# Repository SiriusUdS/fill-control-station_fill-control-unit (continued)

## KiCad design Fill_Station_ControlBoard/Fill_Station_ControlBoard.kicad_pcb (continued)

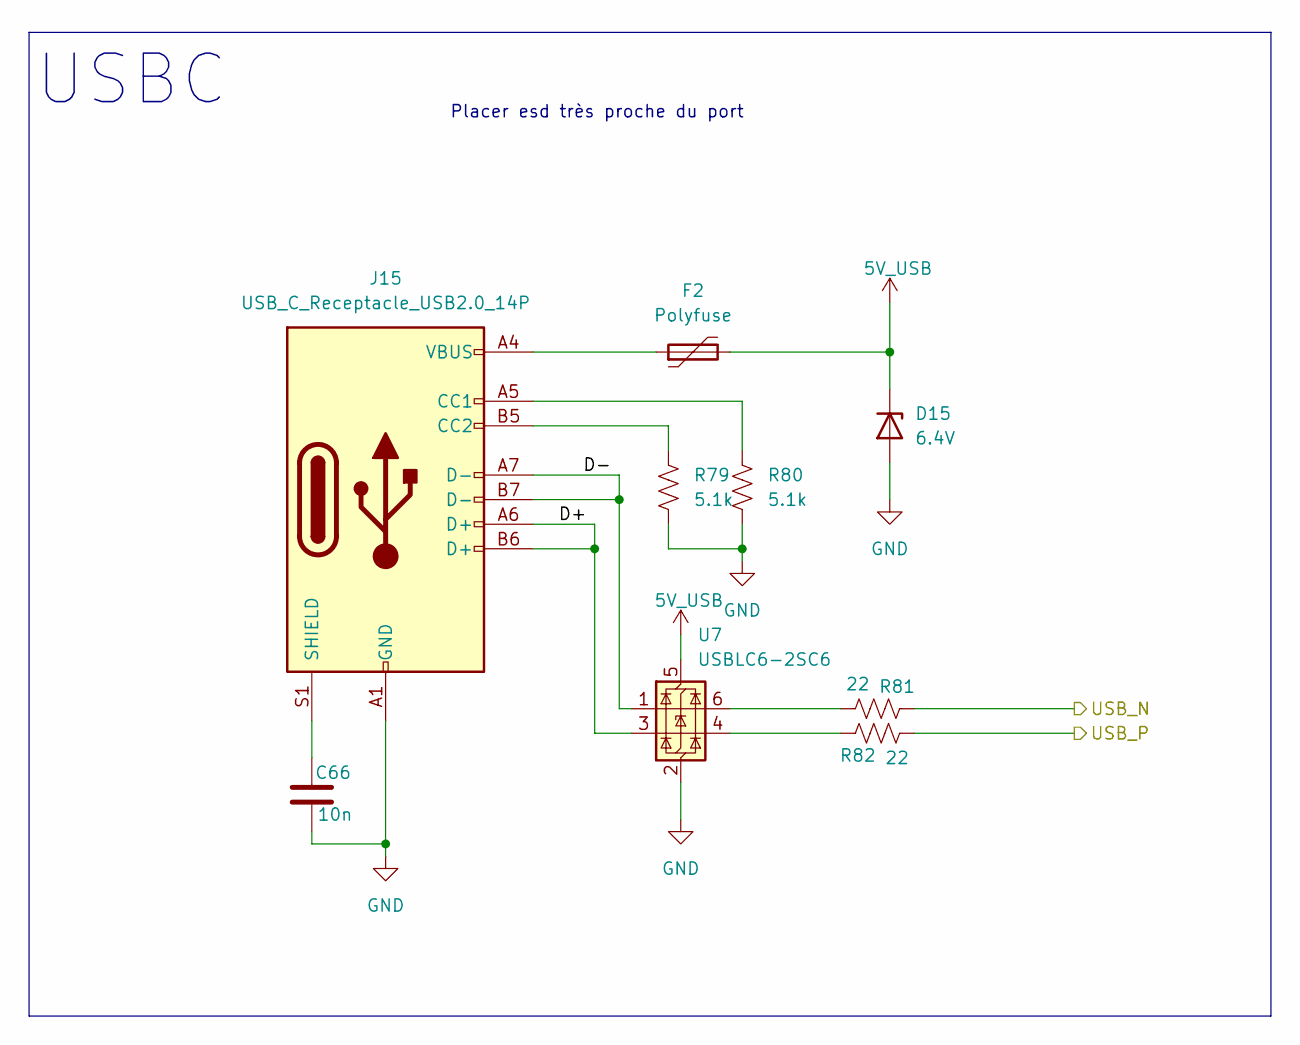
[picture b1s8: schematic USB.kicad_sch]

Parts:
C66: 10n; C_0603_1608Metric; LCSC C100042
D15: 6.4V; D_SOD-123; LCSC C79598
F2: Polyfuse; Fuse_1206_3216Metric; LCSC C70083
J15: USB_C_Receptacle_USB2.0_14P; USB_C_Receptacle_GCT_USB4105-xx-A_16P_TopMnt_Horizontal; LCSC C393939
R79, R80: 5.1k; R_0402_1005Metric; LCSC C25905
R81, R82: 22; R_0402_1005Metric; LCSC C25092
U7: USBLC6-2SC6; SOT-23-6; LCSC C7519

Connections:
5V_USB: D15.1 (K), F2.2, U7.5 (VBUS); also elsewhere on the board
/MCU/USBC.DM: R81.1; also elsewhere on the board
/MCU/USBC.DP: R82.2; also elsewhere on the board
/USB/D+: J15.A6 (D+), J15.B6 (D+), U7.3 (I/O2)
/USB/D-: J15.A7 (D-), J15.B7 (D-), U7.1 (I/O1)
GND: C66.2, D15.2 (A), J15.A1 (GND), J15.A12 (GND), J15.B1 (GND), J15.B12 (GND), R79.2, R80.2, U7.2 (GND); also elsewhere on the board
unnamed: F2.1, J15.A4 (VBUS), J15.A9 (VBUS), J15.B4 (VBUS), J15.B9 (VBUS)
unnamed: J15.A5 (CC1), R80.1
unnamed: J15.B5 (CC2), R79.1
unnamed: C66.1, J15.S1 (SHIELD)
unnamed: R81.2, U7.6 (I/O1)
unnamed: R82.1, U7.4 (I/O2)

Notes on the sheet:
Placer esd très proche du port
USBC

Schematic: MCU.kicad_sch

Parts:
BT1: RTC_BAT; Battery_Panasonic_CR2032-HFN_Horizontal_CircularHoles; Manufacturer Part Number BHX1-1025-SM; LCSC C910763
C16, C23, C25, C26, C27, C28, C29, C30, C31, C33, C34, C35, C36, C37, C39, C40, C41, C42, C43, C44, C46, C48, C83, C90, C91: 100n; C_0402_1005Metric; LCSC C60474
C17, C18, C19, C21: 2.2u; C_0603_1608Metric
C20: 100n; C_0603_1608Metric; LCSC C14663
C22, C45, C47, C50, C53: 1u; C_0603_1608Metric; LCSC C59302
C24, C54: 4.7u; C_0603_1608Metric; LCSC C108342
C49, C52, C87: 10u; C_0603_1608Metric; LCSC C22399626
C51: *; C_0402_1005Metric; not fitted
C88: 100u; C_0805_2012Metric; LCSC C141660
FID1, FID2, FID3: Fiducial; Fiducial_0.5mm_Mask1mm
H1, H2, H3, H4: M3_Hole_With_Spacer_H10mm; MountingHole_3.2mm_With_Spacer_H10mm
J12: Conn_02x05_Counter_Clockwise; PinSocket_2x05_P2.00mm_Vertical
L2: L_Ferrite; R_0402_1005Metric; LCSC C160977
R49, R50: 10k; R_0603_1608Metric
R51, R53: 10k; R_0402_1005Metric; LCSC C173683
R52: 10k; C_0402_1005Metric; LCSC C173683
R54: 0; R_0402_1005Metric; LCSC C17168
R89, R103, R113, R114: 22; R_0402_1005Metric; LCSC C25092
SW1: RESET; SW_DPDT_CK_JS202011JCQN; LCSC C221666
SW2: BOOT; SW_DPDT_CK_JS202011JCQN; LCSC C221666
U2: STM32H747IITx; LQFP-176_24x24mm_P0.5mm; LCSC C730199
Y1: ASV-25.000MHz; Oscillator_SMD_Abracon_ASV-4Pin_7.0x5.1mm; LCSC C1987509
Y2: ASV-32.768kHz; Oscillator_SMD_Abracon_ASV-4Pin_7.0x5.1mm; LCSC C17591433

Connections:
3V3: C24.1, C25.1, C26.1, C27.1, C28.1, C29.1, C30.1, C31.1, C33.1, C34.1, C35.1, C36.1, C37.1, C39.1, C40.1, C41.1, C42.1, C43.1, C44.1, C45.1, C46.1, C47.1, C48.1, C49.1, C50.1, C52.1, C53.1, C54.1, C87.1, C88.1, J12.1, L2.2, R51.1, R52.1, R53.1, SW1.3 (C), SW2.3 (C), U2.7 (VDD), U2.13 (VDD), U2.16 (VDDSMPS), U2.25 (VDD), U2.44 (VDD), U2.48 (VDD), U2.65 (VDD), U2.71 (VDD), U2.82 (VDDLDO), U2.84 (VDD), U2.92 (VDD), U2.99 (VDD), U2.113 (VDD), U2.121 (VDD33_USB), U2.126 (VDD), U2.135 (VDDLDO), U2.136 (VDD), U2.152 (VDD), U2.160 (VDD), U2.175 (VDDLDO), U2.176 (VDD), Y1.4 (Vdd), Y2.4 (Vdd); also elsewhere on the board
3V3A: C16.1, C83.1, L2.1, U2.39 (VREF+), U2.40 (VDDA)
5V: C22.1, C23.1, U2.120 (VDD50_USB); also elsewhere on the board
/Alimentation/LED1: U2.19 (PF1); also elsewhere on the board
/Alimentation/LED2: U2.20 (PF2); also elsewhere on the board
/Alimentation/LED3: U2.21 (PF3); also elsewhere on the board
/Alimentation/PM_CRIT: U2.59 (PF12); also elsewhere on the board
/Alimentation/PM_SCL: U2.61 (PF14); also elsewhere on the board
/Alimentation/PM_SDA: U2.62 (PF15); also elsewhere on the board
/Alimentation/PM_TC: U2.63 (PG0); also elsewhere on the board
/Alimentation/PM_WARN: U2.60 (PF13); also elsewhere on the board
/CAN FD/CAN.RXD: U2.168 (PB8); also elsewhere on the board
/CAN FD/CAN.TXD: R89.2; also elsewhere on the board
/Control/BUZZ: U2.91 (PD10); also elsewhere on the board
/Control/E-match1: U2.95 (PD12); also elsewhere on the board
/Control/E-match1_Cont: U2.89 (PD8); also elsewhere on the board
/Control/E-match1_Det: U2.96 (PD13); also elsewhere on the board
/Control/E-match2: U2.97 (PD14); also elsewhere on the board
/Control/E-match2_Cont: U2.90 (PD9); also elsewhere on the board
/Control/E-match2_Det: U2.98 (PD15); also elsewhere on the board
/Control/GPIO1: U2.1 (PE2); also elsewhere on the board
/Control/GPIO2: U2.2 (PE3); also elsewhere on the board
/Control/GPIO3: U2.3 (PE4); also elsewhere on the board
/Control/GPIO4: U2.4 (PE5); also elsewhere on the board
/Control/GPIO5: U2.5 (PE6); also elsewhere on the board
/Control/Servo.Signal1: U2.69 (PE9); also elsewhere on the board
/Control/Servo.Signal2: U2.68 (PE8); also elsewhere on the board
/Control/Servo.Signal3: U2.67 (PE7); also elsewhere on the board
/Ethernet/Eth.CRS_DV: U2.52 (PA7); also elsewhere on the board
/Ethernet/Eth.MDC: U2.35 (PC1); also elsewhere on the board
/Ethernet/Eth.MDIO: U2.43 (PA2); also elsewhere on the board
/Ethernet/Eth.REFCLKO: U2.42 (PA1); also elsewhere on the board
/Ethernet/Eth.RST: U2.51 (PA6); also elsewhere on the board
/Ethernet/Eth.RXD_N: U2.54 (PC5); also elsewhere on the board
/Ethernet/Eth.RXD_P: U2.53 (PC4); also elsewhere on the board
/Ethernet/Eth.TXD_N: R114.2; also elsewhere on the board
/Ethernet/Eth.TXD_P: R113.2; also elsewhere on the board
/Ethernet/Eth.TXEN: R103.2; also elsewhere on the board
/MCU/Boot: R50.2, U2.167 (BOOT0)
/MCU/Clock_25Mhz: C51.1, R54.2, U2.31 (PH0)
/MCU/Clock_32.768khz: U2.10 (PC14), Y2.3 (OUT)
/MCU/I2C1.SCL: U2.165 (PB6); also elsewhere on the board
/MCU/I2C1.SDA: U2.166 (PB7); also elsewhere on the board
/MCU/IO: J12.4, U2.144 (PD1)
/MCU/NRST: J12.6, R49.2, U2.33 (NRST)
/MCU/SD1.CLK: U2.142 (PC12); also elsewhere on the board
/MCU/SD1.CMD: U2.145 (PD2); also elsewhere on the board
/MCU/SD1.DAT0: U2.124 (PC8); also elsewhere on the board
/MCU/SD1.DAT1: U2.125 (PC9); also elsewhere on the board
/MCU/SD1.DAT2: U2.140 (PC10); also elsewhere on the board
/MCU/SD1.DAT3: U2.141 (PC11); also elsewhere on the board
/MCU/SD2.CLK: U2.149 (PD6); also elsewhere on the board
/MCU/SD2.CMD: U2.150 (PD7); also elsewhere on the board
/MCU/SD2.DAT0: U2.87 (PB14); also elsewhere on the board
/MCU/SD2.DAT1: U2.88 (PB15); also elsewhere on the board
/MCU/SD2.DAT2: U2.162 (PB3); also elsewhere on the board
/MCU/SD2.DAT3: U2.163 (PB4); also elsewhere on the board
/MCU/SD2.DET: U2.147 (PD4); also elsewhere on the board
/MCU/SD.DET: U2.116 (PG6); also elsewhere on the board
/MCU/SPI4.CS: U2.77 (PE15); also elsewhere on the board
/MCU/SPI4.MISO: U2.75 (PE13); also elsewhere on the board
/MCU/SPI4.MOSI: U2.76 (PE14); also elsewhere on the board
/MCU/SPI4.SCK: U2.74 (PE12); also elsewhere on the board
/MCU/SPI5.CS: U2.155 (PG11); also elsewhere on the board
/MCU/SPI5.MISO: U2.156 (PG12); also elsewhere on the board
/MCU/SPI5.MOSI: U2.158 (PG14); also elsewhere on the board
/MCU/SPI5.SCK: U2.157 (PG13); also elsewhere on the board
/MCU/SWCLK: J12.9, U2.138 (PA14)
/MCU/SWDIO: J12.10, U2.132 (PA13)
/MCU/USBC.DM: U2.130 (PA11); also elsewhere on the board
/MCU/USBC.DP: U2.131 (PA12); also elsewhere on the board
GND: BT1.2 (-), C16.2, C17.2, C18.2, C19.2, C20.2, C21.2, C22.2, C23.2, C24.2, C25.2, C26.2, C27.2, C28.2, C29.2, C30.2, C31.2, C33.2, C34.2, C35.2, C36.2, C37.2, C39.2, C40.2, C41.2, C42.2, C43.2, C44.2, C45.2, C46.2, C47.2, C48.2, C49.2, C50.2, C51.2, C52.2, C53.2, C54.2, C83.2, C87.2, C88.2, C90.2, C91.2, H1.1, H2.1, H3.1, H4.1, J12.2, J12.3, J12.5, SW1.1 (A), SW2.1 (A), U2.6 (VSS), U2.12 (VSS), U2.14 (VSSSMPS), U2.24 (VSS), U2.38 (VSSA), U2.45 (VSS), U2.47 (VSS), U2.64 (VSS), U2.70 (VSS), U2.81 (VSS), U2.83 (VSS), U2.93 (VSS), U2.100 (VSS), U2.103 (DSI_D0P), U2.104 (DSI_D0N), U2.105 (VSSDSI), U2.106 (DSI_CKP), U2.107 (DSI_CKN), U2.109 (VSSDSI), U2.112 (VSS), U2.119 (VSS), U2.134 (VSS), U2.137 (VSS), U2.151 (VSS), U2.159 (VSS), U2.173 (VSS), Y1.2 (GND), Y2.2 (GND); also elsewhere on the board
unnamed: C17.1, U2.80 (VCAP)
unnamed: C18.1, U2.133 (VCAP)
unnamed: C19.1, U2.172 (VCAP)
unnamed: C91.1, R49.1, SW1.2 (B)
unnamed: C90.1, R50.1, SW2.2 (B)
unnamed: R89.1, U2.169 (PB9)
unnamed: R103.1, U2.79 (PB11)
unnamed: R113.1, U2.85 (PB12)
unnamed: R114.1, U2.86 (PB13)
unnamed: R51.2, U2.174 (PDR_ON)
unnamed: BT1.1 (+), C20.1, U2.8 (VBAT)
unnamed: C21.1, U2.101 (VCAPDSI)
unnamed: R52.2, Y1.1 (EN)
unnamed: R54.1, Y1.3 (OUT)
unnamed: R53.2, Y2.1 (EN)

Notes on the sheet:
Solder
BOOT
EXTERNAL OSCILLATOR
RESET
SWD
Mechanical
DECOUPLING MCU
Microchip Pinout
Plastic stand-off

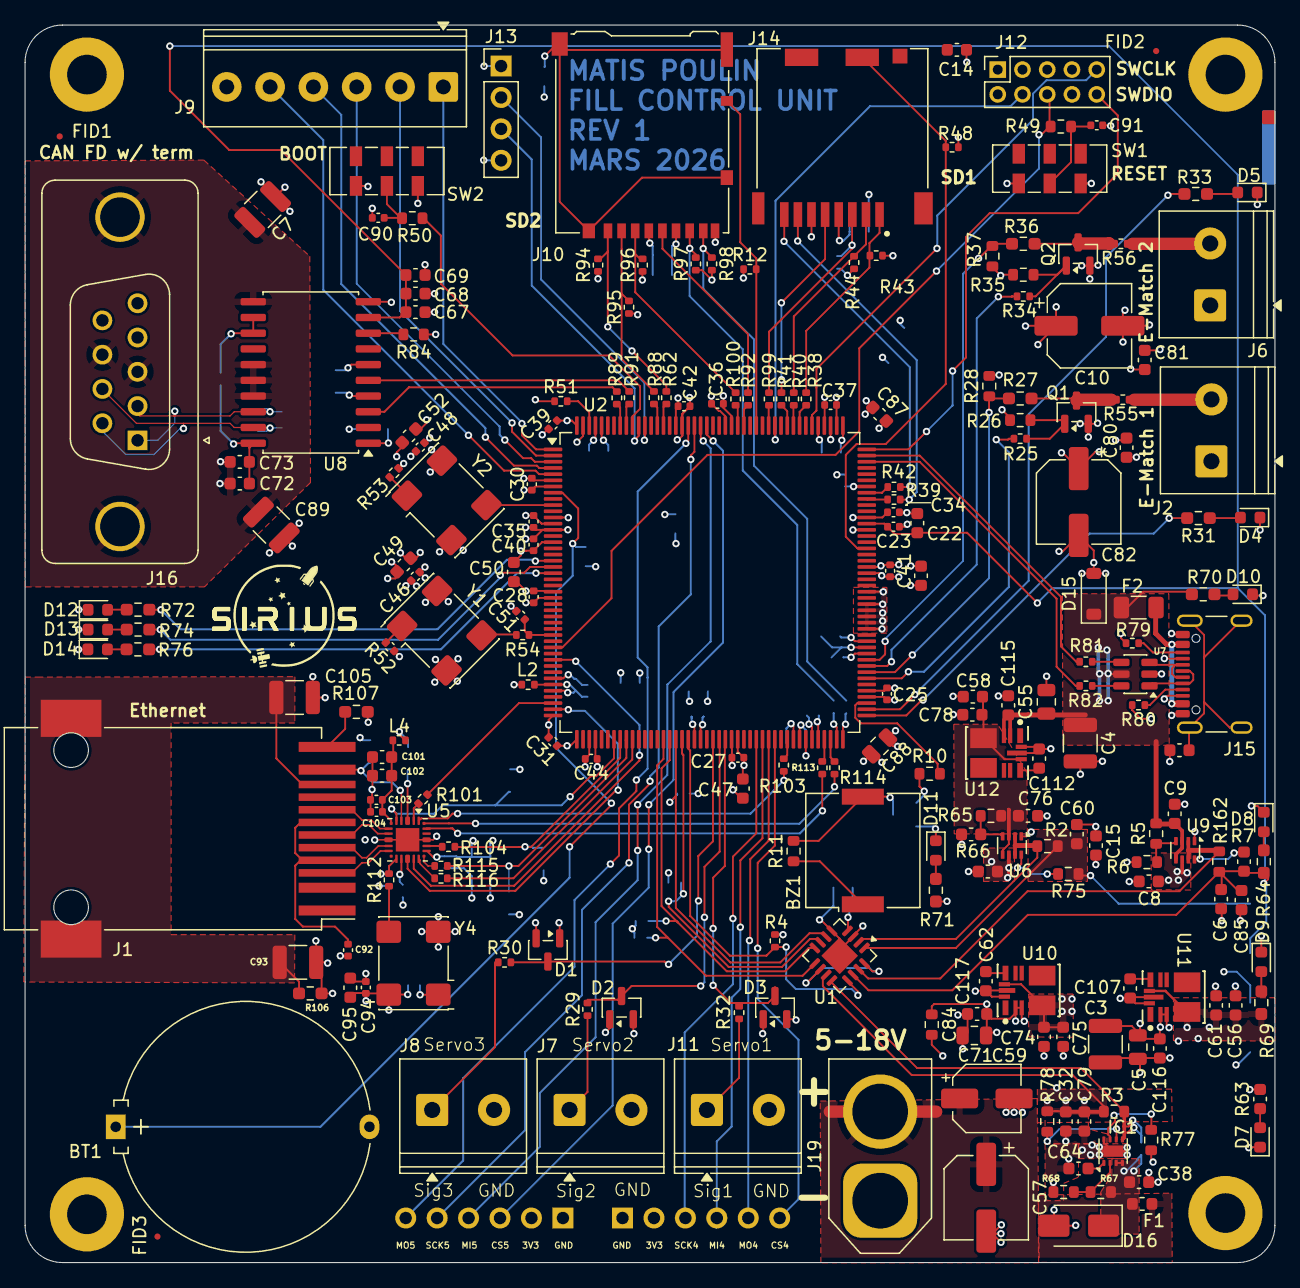
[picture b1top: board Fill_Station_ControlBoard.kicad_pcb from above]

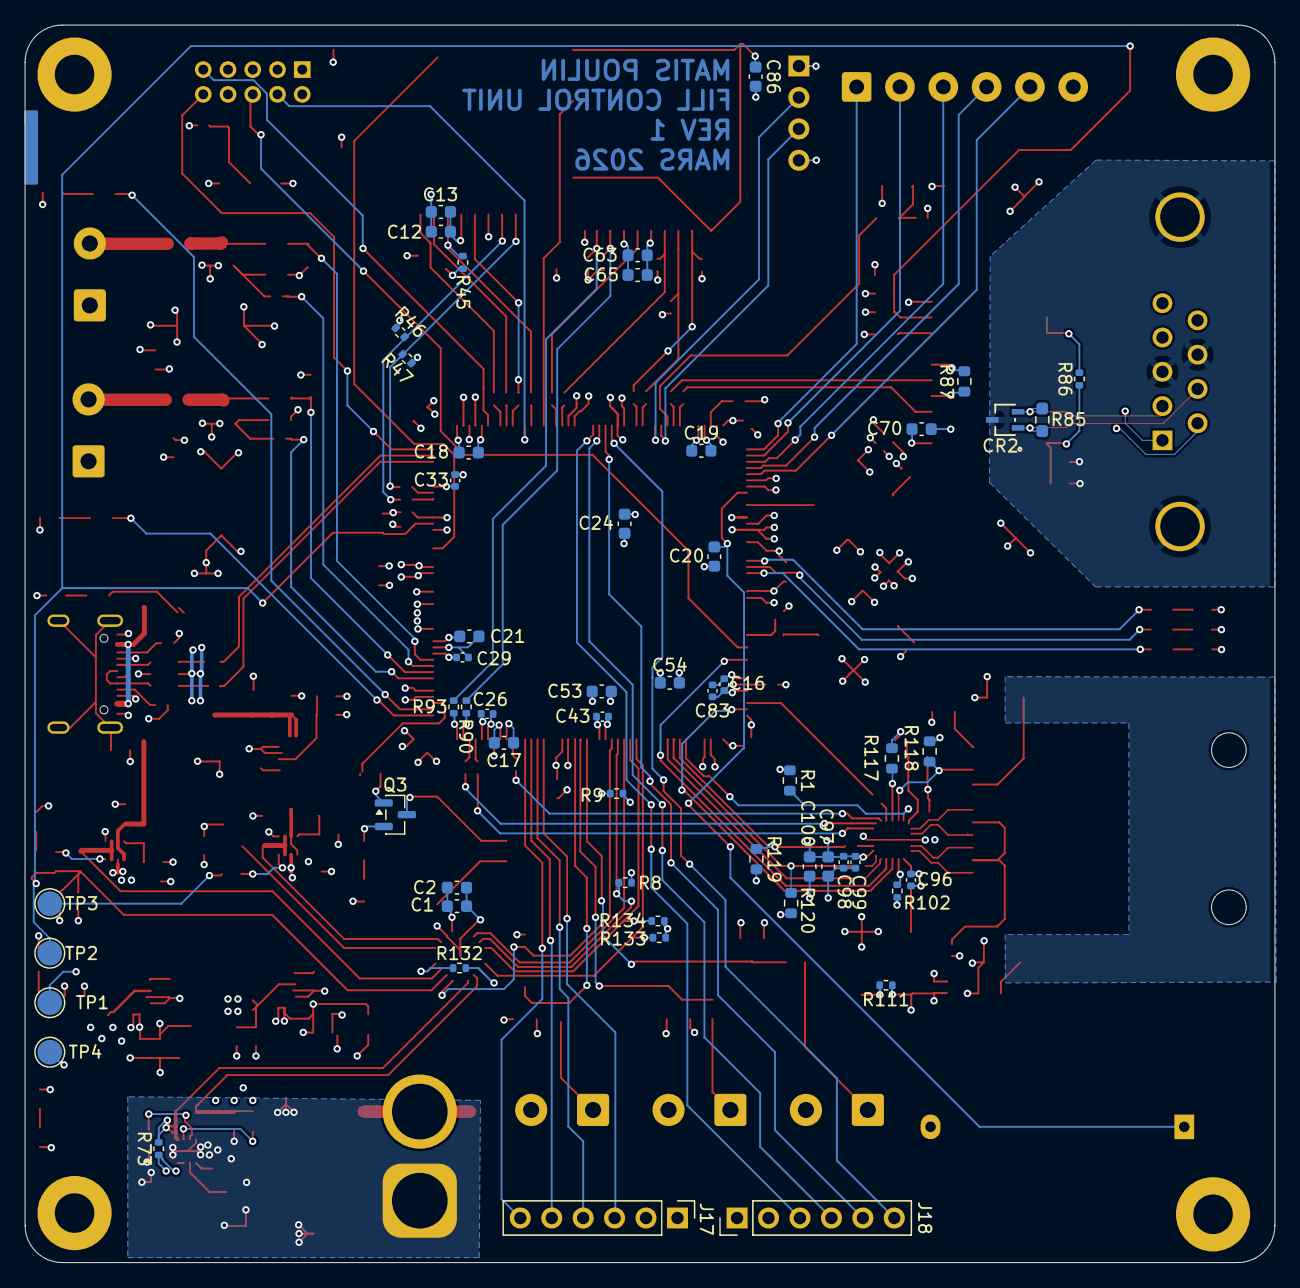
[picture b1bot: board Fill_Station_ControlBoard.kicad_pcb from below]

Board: 6 copper layers, 101.0 x 100.0 mm, 279 parts (56 on the bottom side), 179 nets.

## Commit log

2025-12-02 First upload
    Juste avoir des fichier
2025-12-08 1282025BASEBOARD
2025-12-09 1282025PostRéu
2025-12-09 2025/12/08 - Sch Ethernet
2026-01-13 10122026
2026-01-15 14012026
2026-01-24 Restructure + phy ethernet
    Finaliser le phy ethernet et changé pour hyerarchical sheets
2026-01-24 petites modifs pour ethernet + usb
2026-01-24 heater
2026-01-26 Développer plus le circuit CAN
2026-02-09 Ajouter schema de JTAG
2026-02-15 Changement de CAN et quelques trucs
2026-02-15 Assignation footprint pis valeurs resistances del
2026-02-17 Fait des trucs (commencer arrangement de pièces sur PCB
2026-02-17 Vince
2026-02-17 arthur
2026-02-18 Modifs de l'organisation des pages
2026-02-18 début layout
2026-02-21 Ajout power
2026-02-21 Ajout de footprint
2026-02-21 Changement val Resistance a 10k
2026-02-23 wiring de certaines parties du PCB et placement de quelques composantes sur le PCB
2026-02-24 Petits correctifs
2026-02-24 Petits changements et truc que j'ai fait lundi
2026-02-26 PCB fait
2026-03-03 Travail Layout
2026-03-04 PCB presque terminé
    Modifs de l'alim
2026-03-07 finalisé le pcb
2026-03-17 PCB fini avant review avec greg
2026-03-22 Final_V1
